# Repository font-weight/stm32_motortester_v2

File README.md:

# Мотортестер V2

Учебный проект одноканального мотортестера для Windows 10: приложение, прошивка
STM32F103C8T6 и материалы аналогового входа. Текущий этап приложения — **V2-21**.
Один физический канал **CH1**, профили **«Осциллограф» / «Зажигание»**,
живой график, запись и анализ в одном окне с крутилками.

Публикуются исходники. Для запуска используйте команды ниже; наличие готового
публичного EXE-релиза эта инструкция не предполагает. Фактические проверки
и аппаратные ограничения собраны в [прогрессе проекта](docs/progress.md).

На снимке — учебная запись, не измерение катушки.

## Что умеет приложение

- Получать поток STM32 через USB / COM-порт: 50 или 100 тыс. отсчётов/с
  с сохранением 12 бит; 150 тыс. отсчётов/с с сохранением 10 бит, если режим
  поддерживает прошивка. Это частота дискретизации, а не полоса аналогового входа.
- Записывать поток, открывать записи, сохранять отдельный захват, экспортировать
  CSV + JSON. Исходные коды, разрывы и профиль входа сохраняются.
- Масштабировать график, измерять курсорами A–B, находить пороговые события,
  удерживать их в кадре и переходить между ними без остановки записи.
- Показывать Min / Max / размах, среднее DC, период и частоту видимого участка,
  а также отдельную частоту найденных событий в живом приёме.
- Настраивать расчётную шкалу CH1 и выполнять отдельную калибровку DC / AC
  с контрольной точкой, сохранением исходных данных и отчётом PDF.
- Оценивать частоту и затухание колебаний на выбранном участке, показывать
  исходные пики и сводку серии событий. Это анализ сигнала, не диагноз катушки.

## Быстрый запуск из исходников

Нужны Windows x64, Git и обычный **CPython 3.14.7 x64** с командой `py`.
В PowerShell выполните:

```powershell
git clone https://github.com/font-weight/stm32_motortester_v2.git
cd stm32_motortester_v2
py -3.14 -m venv .venv
.\.venv\Scripts\python.exe -m pip install -r host\requirements-gui.txt
.\run_v2.cmd
```

Интернет нужен для получения исходников и зависимостей. Активировать `.venv`
не требуется. Для следующих запусков достаточно открыть **`run_v2.cmd`**.
Если скачали репозиторий через **Code → Download ZIP**, распакуйте его,
откройте PowerShell в полученной папке и начните с команды создания `.venv`.

Приложение открывается без подключения и без автоматически запущенного ДЕМО.
[Другие команды запуска и сведения для разработчика](host/README.md).

## Попробовать без платы

Откройте **«Сервис → ДЕМО для проверки → Осциллограф»** или **«Зажигание»**.
Можно менять развёртку, включать курсоры и делать учебные записи.
ДЕМО явно обозначено и не использует COM-порт.

Для нового анализа выберите **«Сервис → ДЕМО для проверки → Затухающие
колебания · учебная запись»**, затем внизу окна включите
**«Затухающие колебания»**, нажмите **«Предложить участок»**, осмотрите его
и нажмите **«Рассчитать»**. У искусственного примера заданы 2500 Гц и τ = 1,2 мс.
[Что означают показатели и когда расчёт недоступен](docs/ringdown.md).

Мастер **«Калибровка…»** находится справа. Источник **«Учебный поток · без платы»**
позволяет пройти его без аппаратуры; такой результат нельзя применить к прибору.
[Пошаговая инструкция калибровки](docs/calibration-wizard.md).

## Подключить STM32 и записать сигнал

Нужна плата с совместимой прошивкой V2; приложение само её не прошивает.
Поддерживаемые режимы определяются при подключении. Подробности —
[протокол и пакетный приём](docs/streaming-batch1024.md).

1. В верхней строке выберите COM-порт и частоту, нажмите **«Подключить»**.
   Приём начинается отдельно.
2. Если аналоговый тракт ещё не подключён, оставьте **«Прямой PA0 / неизвестный
   вход»**: будут показаны коды АЦП. Для подключённого входа R5 выберите справа
   фактический режим **DC + WIDE**, **AC + WIDE** или **AC + SENSITIVE**.
   Раскройте **«Настройка входа»**, укажите экземпляр платы, подтвердите положения
   физических переключателей и нажмите **«Применить вход»**.
3. Задайте **«Уровень запуска»**, **«Пауза запуска»** и остальные параметры
   поиска, затем нажмите **«Применить поиск»** и **«Живой поток»**.
4. Для сохранения нажмите **«Начать запись…»** и выберите новое имя `.mtstream`.
   **«Пауза просмотра»** удерживает график; приём и запись продолжаются.
5. **«Остановить»** завершает приём. Кнопка **«Открыть запись…»** открывает
   `.mtstream`, `.mtshot`, `.mtv2` и `.mtcap` в том же окне.
   Для нового подключения снова используйте **«Подключить»**.

Файл `.mtstream` храните вместе с соседним `.mtstream.v2.json`, содержащим
контекст и профиль. Просмотр и экспорт не изменяют оригинал.
[Полная инструкция главного окна](docs/unified-ui.md).

## Напряжение и аппаратные границы

В/мВ означают напряжение на **разъёме CH1 перед входным делителем**.
Это не напряжение на ножке АЦП и не киловольты вторичной цепи зажигания.
Неизвестный вход остаётся в кодах АЦП. Расчётная шкала не является калибровкой;
каждый режим имеет свои коэффициенты. AC не измеряет постоянную составляющую.

Профиль «Осциллограф» / «Зажигание» не переключает физические S1/S2.
DC + SENSITIVE не принят как рабочий режим. Подготовка программы и схемы
не подтверждает защиту, допустимое напряжение, полосу или готовность к автомобилю.
Для аппаратных действий используйте [первое включение R53](docs/guides/r53-first-power-ru.md)
и [условия физической проверки](docs/validation.md).

## Где искать подробности

| Задача | Документ |
| --- | --- |
| Управление, запись, захват и курсоры | [Главное окно](docs/unified-ui.md) |
| Режимы и пересчёт напряжения | [Аналоговый вход](docs/stream-analog-input.md) |
| Калибровка DC / AC, исходные данные и PDF | [Мастер калибровки](docs/calibration-wizard.md) |
| Показатели графика и частота событий | [Видимый участок](docs/segment-measurements.md), [события](docs/event-frequency.md) |
| Анализ затухающих колебаний | [Инструкция](docs/ringdown.md) |
| Самодельный ёмкостной датчик | [Сборка датчика](docs/guides/capacitive-pickup-ru.md) |
| Продолжение разработки | [Текущая задача](task.md), [требования](requirements.md), [решения](docs/decisions.md), [прогресс](docs/progress.md) |

Код приложения — `host/motortester/v2/`, прошивка — `firmware/`, аппаратные
материалы — `hardware/`, исходные задания — `docs/design/`. Правила изменений
и приёмки — [AGENTS.md](AGENTS.md) и [quality-gate](docs/quality-gate.md).
Состав опубликованных исходных материалов и актуальный проект платы пояснены
в [памятке к публикации](docs/design/PUBLICATION_RU.md).
Исходный [stm32_motortester](https://github.com/font-weight/stm32_motortester)
сохраняется как источник прежних наработок; разработка ведётся в этом V2-репозитории.

Лицензии имеют ограниченную область: [host/LICENSE](host/LICENSE) не назначает
MIT всему репозиторию или каталогу V2; см. [точный перечень](host/docs/project-license.md).
Публичный бинарный выпуск требует отдельной [проверки лицензий зависимостей](host/packaging/LICENSE-REVIEW.md).

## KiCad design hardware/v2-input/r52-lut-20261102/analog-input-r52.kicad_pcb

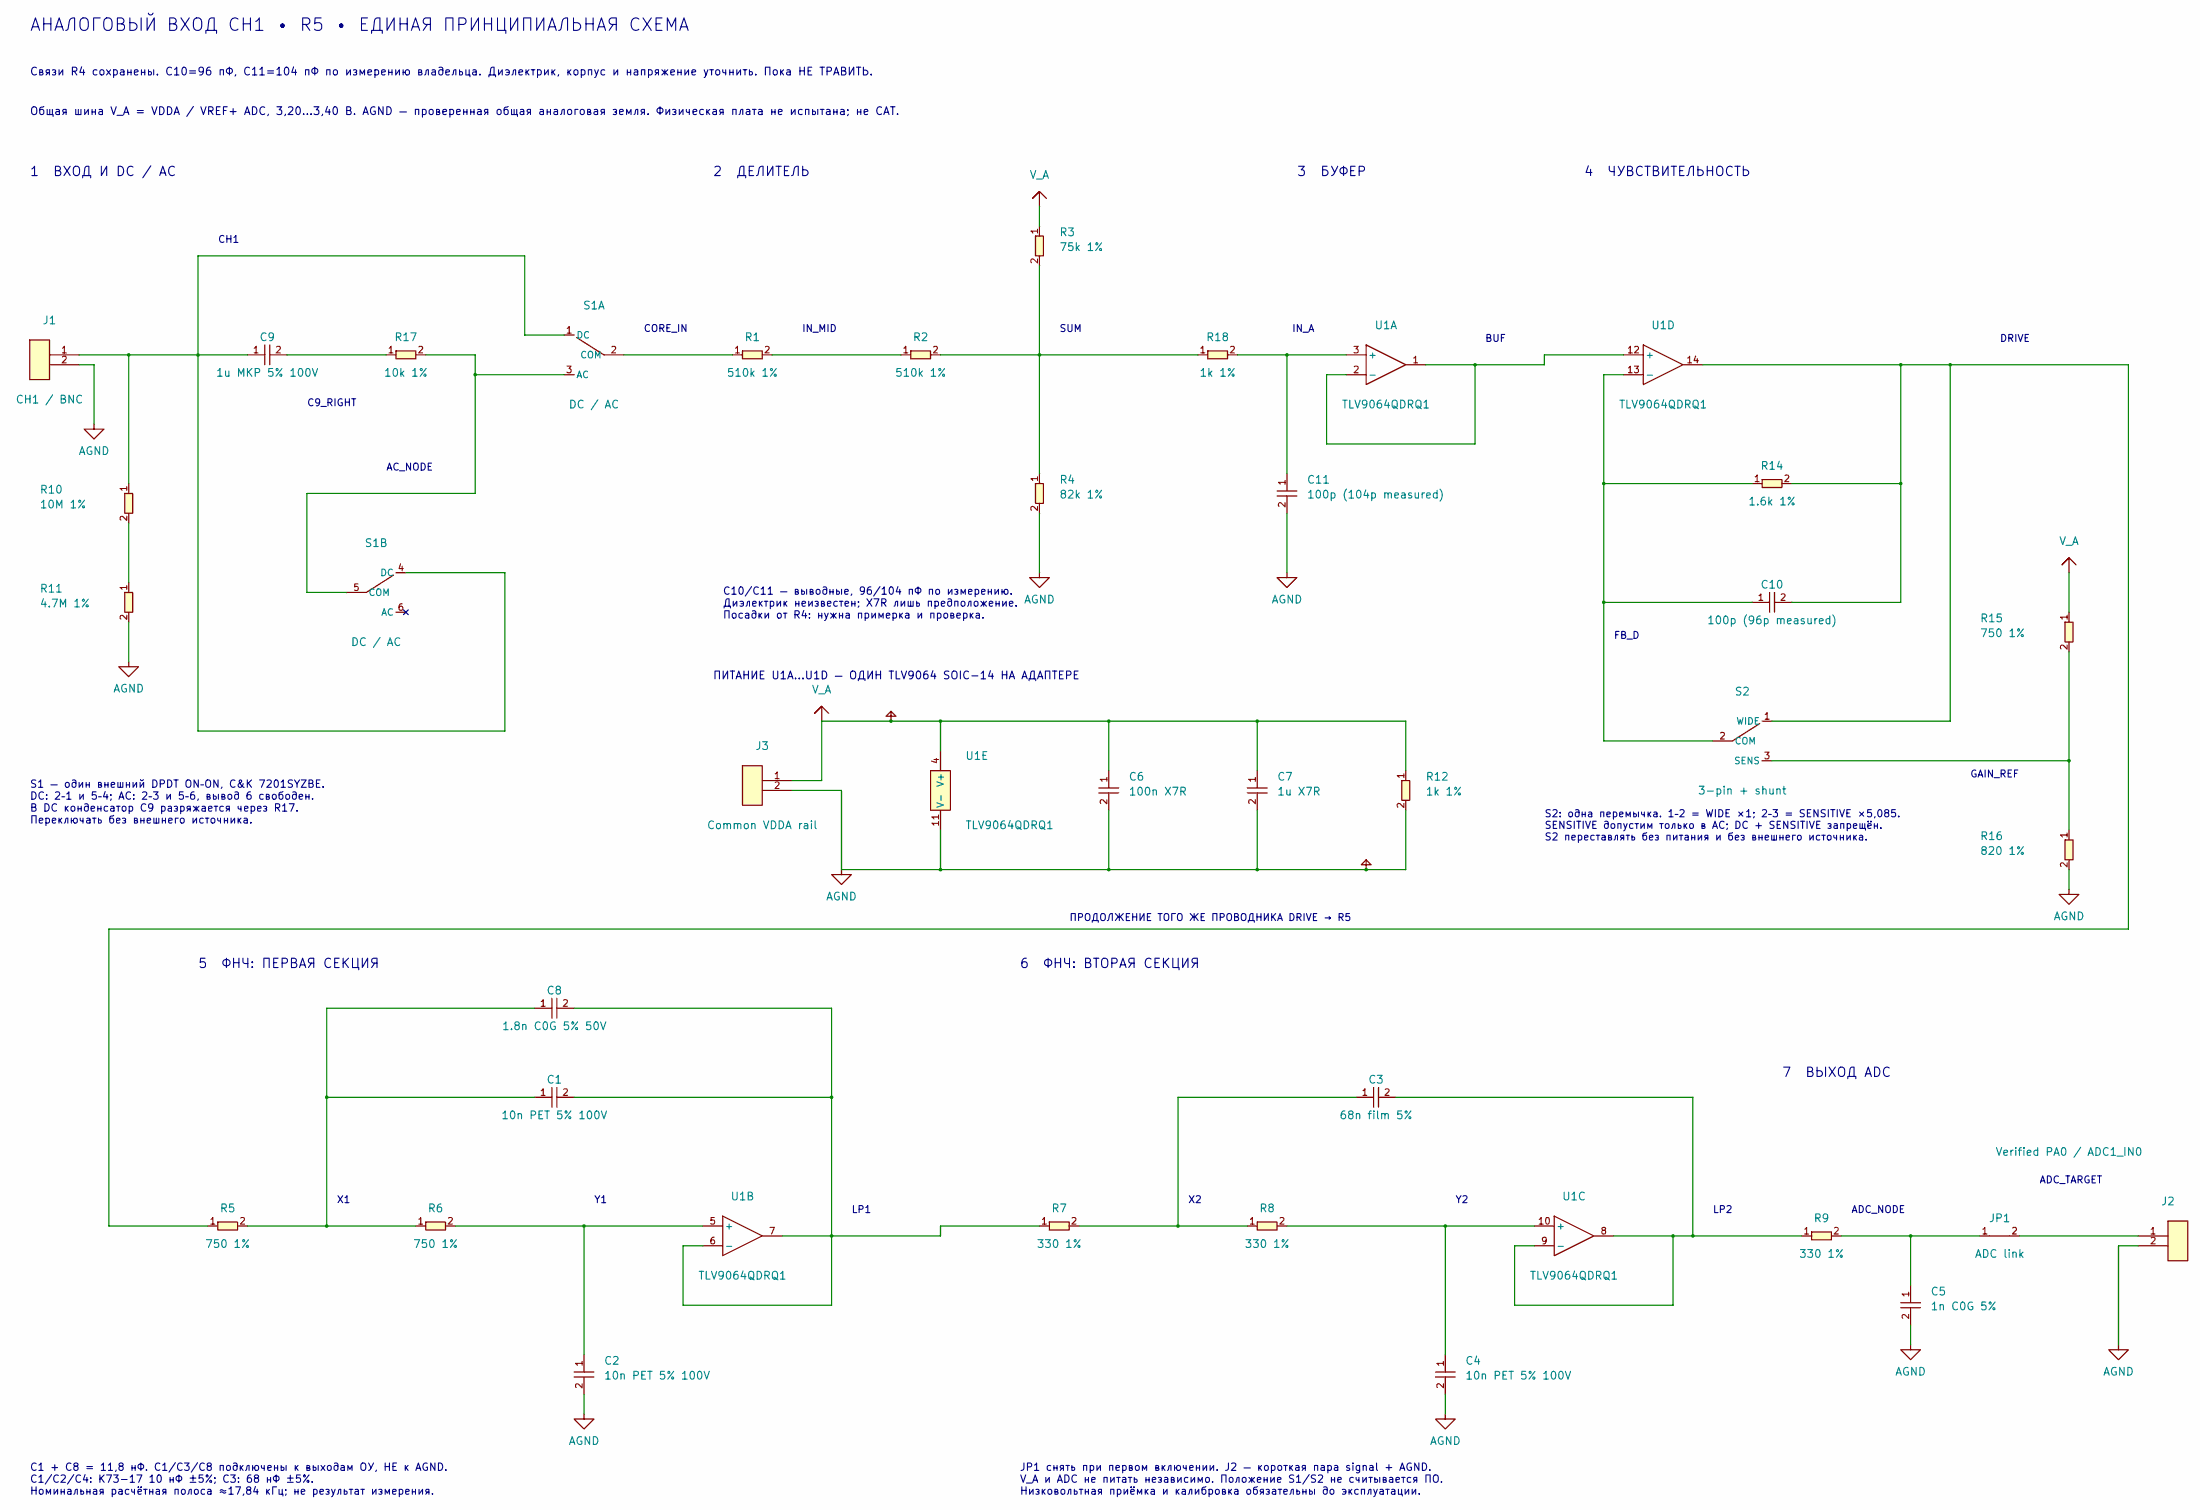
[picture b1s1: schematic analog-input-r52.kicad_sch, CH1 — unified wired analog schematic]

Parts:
C1, C2, C4: 10n PET 5% 100V; Film_K73_P4_LUT
C3: 68n film 5%; Film_P6.5_LUT
C5: 1n C0G 5%; C5_0805_LUT
C6: 100n X7R; Radial_P2.54_LUT
C7: 1u X7R; Radial_P2.54_LUT
C8: 1.8n C0G 5% 50V; Radial_P2.50_LUT
C9: 1u MKP 5% 100V; MKP_P5_7.2x11_LUT
C10: 100p (96p measured); Radial_P2.54_LUT
C11: 100p (104p measured); Radial_P2.54_LUT
J1: CH1 / BNC; Wire_P5.08_LUT
J2: Verified PA0 / ADC1_IN0; Wire_P5.08_LUT
J3: Common VDDA rail; Wire_P5.08_LUT
JP1: ADC link; Shunt_1x2_P2.54_LUT
R1, R2: 510k 1%; R_025W_P10.16_LUT
R3: 75k 1%; R_025W_P10.16_LUT
R4: 82k 1%; R_025W_P10.16_LUT
R5, R6, R15: 750 1%; R_025W_P10.16_LUT
R7, R8, R9: 330 1%; R_025W_P10.16_LUT
R10: 10M 1%; R_025W_P10.16_LUT
R11: 4.7M 1%; R_025W_P10.16_LUT
R12, R18: 1k 1%; R_025W_P10.16_LUT
R14: 1.6k 1%; R_025W_P10.16_LUT
R16: 820 1%; R_025W_P10.16_LUT
R17: 10k 1%; R_025W_P10.16_LUT
S1: DC / AC; DC_AC_Wire_2x3_P5.08
S2: 3-pin + shunt; Shunt_1x3_P2.54_LUT
U1: TLV9064QDRQ1; SOIC14_Adapter_18x18_Rows15.24

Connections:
AGND: C2.2, C4.2, C5.2, C6.2, C7.2, C11.2, J1.2, J2.2, J3.2, R4.2, R11.2, R12.2, R16.2, U1.11 (V-); also elsewhere on the board
unnamed: C1.1, C8.1, R5.2, R6.1
unnamed: C3.1, R7.2, R8.1
unnamed: C5.1, JP1.1, R9.2
unnamed: C9.2, R17.1
unnamed: J2.1, JP1.2
unnamed: R1.2, R2.1
unnamed: R10.2, R11.1
unnamed: R2.2, R3.2, R4.1, R18.1
unnamed: R17.2, S1.3 (AC), S1.5 (COM)
unnamed: R1.1, S1.2 (COM)
unnamed: C9.1, J1.1, R10.1, S1.1 (DC), S1.4 (DC)
unnamed: C10.1, R14.1, S2.2 (COM), U1.13 (-)
unnamed: R15.2, R16.1, S2.3 (SENS)
unnamed 14: C10.2, R5.1, R14.2, S2.1 (WIDE), U1.14; also elsewhere on the board
unnamed: C11.1, R18.2, U1.3 (+)
unnamed: U1.1, U1.2 (-), U1.12 (+)
unnamed: C2.1, R6.2, U1.5 (+)
unnamed: C1.2, C8.2, R7.1, U1.6 (-), U1.7
unnamed: C4.1, R8.2, U1.10 (+)
unnamed: C3.2, R9.1, U1.8, U1.9 (-)
V_A: C6.1, C7.1, J3.1, R3.1, R12.1, R15.1, U1.4 (V+); also elsewhere on the board

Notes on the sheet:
АНАЛОГОВЫЙ ВХОД CH1 • R5 • ЕДИНАЯ ПРИНЦИПИАЛЬНАЯ СХЕМА
Связи R4 сохранены. C10=96 пФ, C11=104 пФ по измерению владельца. Диэлектрик, корпус и напряжение уточнить. Пока НЕ ТРАВИТЬ.
Общая шина V_A = VDDA / VREF+ ADC, 3,20…3,40 В. AGND — проверенная общая аналоговая земля. Физическая плата не испытана; не CAT.
1 ВХОД И DC / AC
2 ДЕЛИТЕЛЬ
3 БУФЕР
4 ЧУВСТВИТЕЛЬНОСТЬ
CH1
C9_RIGHT
AC_NODE
S1 — один внешний DPDT ON–ON, C&K 7201SYZBE. DC: 2–1 и 5–4; AC: 2–3 и 5–6, вывод 6 свободен. В DC конденсатор C9 разряжается через R17. Переключать без внешнего источника.
CORE_IN
IN_MID
SUM
IN_A
BUF
C10/C11 — выводные, 96/104 пФ по измерению. Диэлектрик неизвестен; X7R лишь предположение. Посадки от R4: нужна примерка и проверка.
DRIVE
FB_D
GAIN_REF
S2: одна перемычка. 1–2 = WIDE ×1; 2–3 = SENSITIVE ×5,085. SENSITIVE допустим только в AC; DC + SENSITIVE запрещён. S2 переставлять без питания и без внешнего источника.
ПИТАНИЕ U1A…U1D — ОДИН TLV9064 SOIC-14 НА АДАПТЕРЕ
ПРОДОЛЖЕНИЕ ТОГО ЖЕ ПРОВОДНИКА DRIVE → R5
5 ФНЧ: ПЕРВАЯ СЕКЦИЯ
6 ФНЧ: ВТОРАЯ СЕКЦИЯ
7 ВЫХОД ADC
LP1
LP2
ADC_NODE
ADC_TARGET
C1 + C8 = 11,8 нФ. C1/C3/C8 подключены к выходам ОУ, НЕ к AGND. C1/C2/C4: К73-17 10 нФ ±5%; C3: 68 нФ ±5%. Номинальная расчётная полоса ≈17,84 кГц; не результат измерения.
JP1 снять при первом включении. J2 — короткая пара signal + AGND. V_A и ADC не питать независимо. Положение S1/S2 не считывается ПО. Низковольтная приёмка и калибровка обязательны до эксплуатации.

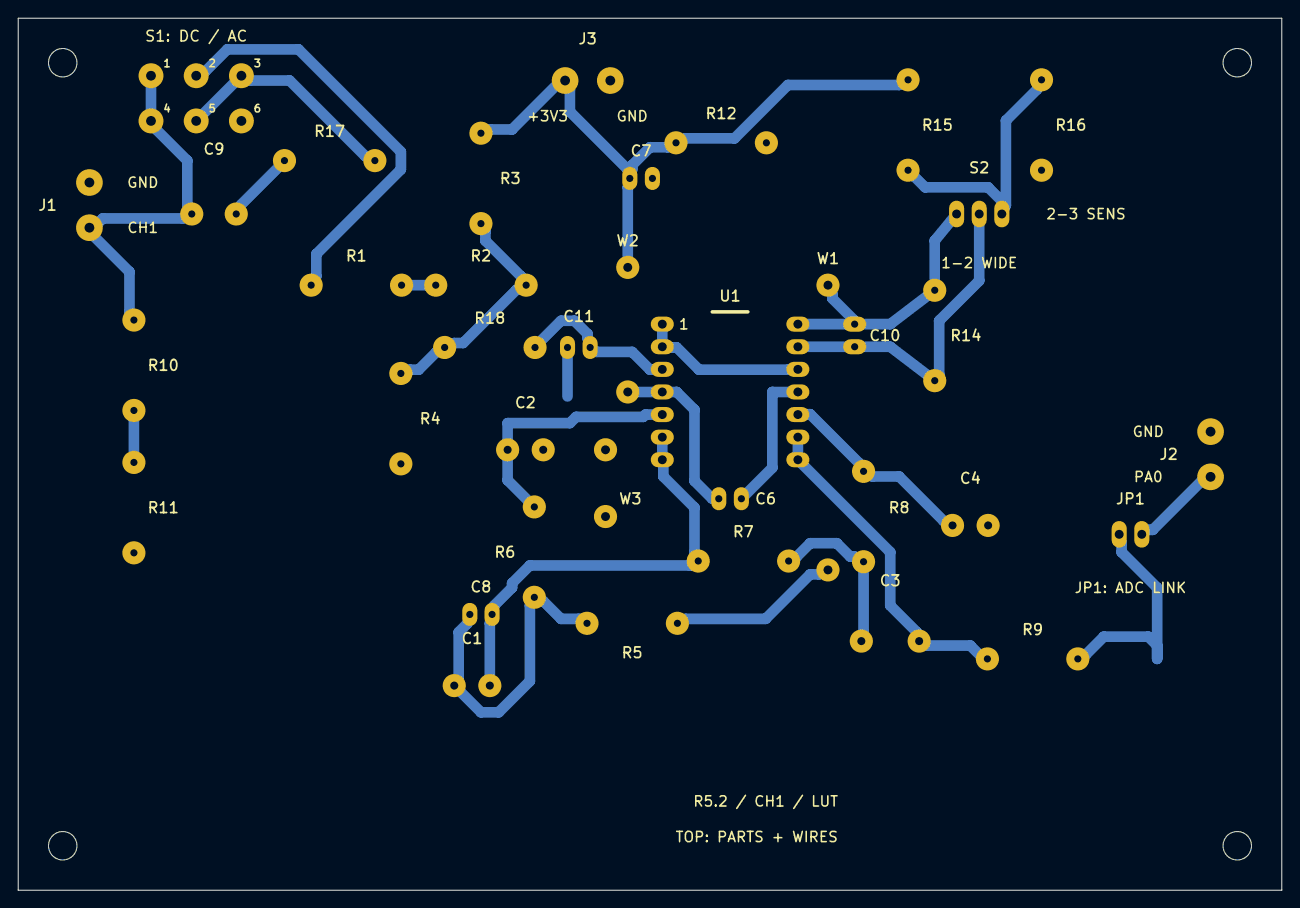
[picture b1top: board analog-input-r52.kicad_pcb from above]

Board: 2 copper layers, 142.0 x 98.0 mm, 42 parts (1 on the bottom side), 22 nets.

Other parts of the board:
H1, H2, H3, H4: M3
W1: Insulated wire; W1_wire
W2: Insulated wire; W2_wire
W3: Insulated wire; W3_wire

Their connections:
AGND: W3.1; also elsewhere on the board
unnamed 14: W1.1; also elsewhere on the board
V_A: W2.1; also elsewhere on the board
